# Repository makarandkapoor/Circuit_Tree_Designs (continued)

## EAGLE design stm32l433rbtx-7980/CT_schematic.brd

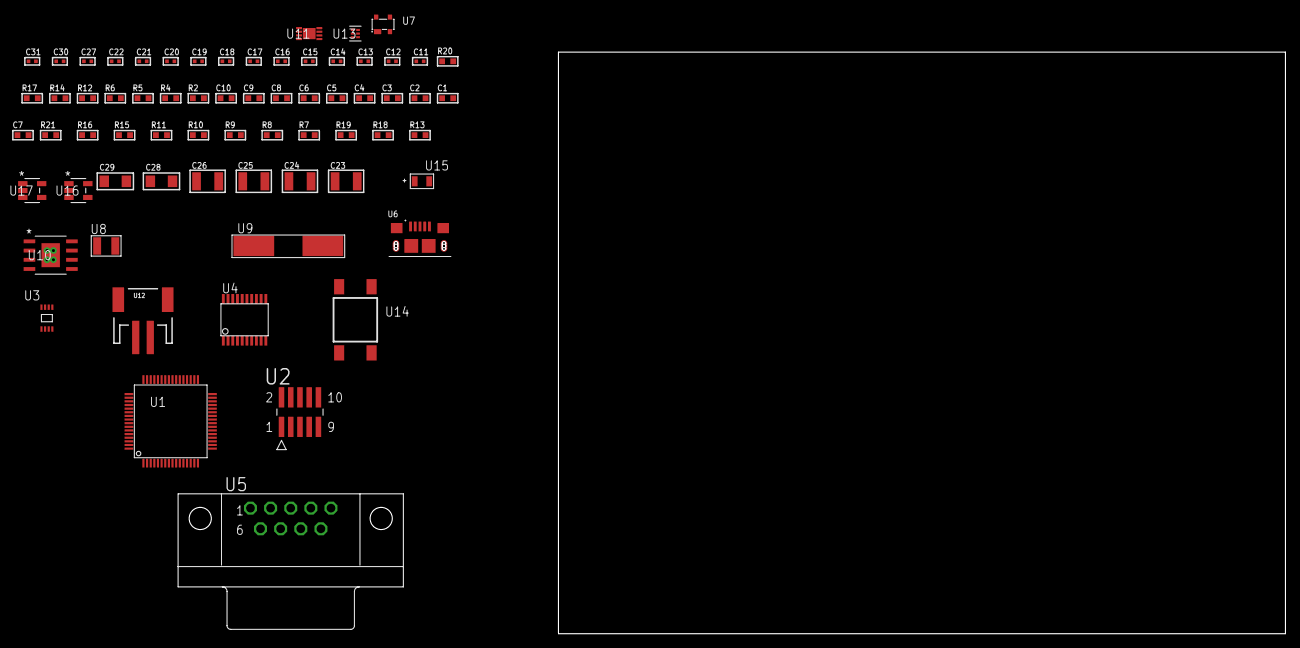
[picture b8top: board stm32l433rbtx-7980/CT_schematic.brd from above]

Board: 2 copper layers, 122.6 x 80.0 mm, 67 parts (0 on the bottom side), 42 nets, no tracks yet.

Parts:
C1, C9: 1e-06; C0603
C2, C3, C4, C5, C6, C10: 1e-07; C0603
C7: 4.7e-06; C0603
C8: 1e-08; C0603
C11, C12, C13, C14: 1e-11; C0402
C15, C17, C18, C19, C20, C21, C22, C27: 1e-07; C0402
C16, C30, C31: 1e-08; C0402
C23, C24, C25, C26: 1e-05; C1210
C28, C29: 1e-05; C1206
R2: 1000.0; R0603
R4: 4700.0; R0603
R5, R6, R14: 2200.0; R0603
R7, R8, R9, R10, R11, R15, R16, R21: 10000.0; R0603
R12: 5.0; R0603
R13: 4031.5447154472; R0603
R17: 9100.0; R0603
R18: 680000.0; R0603
R19: 120000.0; R0603
R20: 2000.0; R0603
U1: STM32L433RBT6; LQFP64
U2: FTSH-105-01-L-DV-K; SAMTEC_FTSH-105-01-L-DV-K
U3: 24AA16-I/MC; TDFN-8/6MM
U4: SP3203ECY-L/TR; TSSOP20-I
U5: 182-009-113R531; 182-009-MALE
U6: 10118193-0001LF; FCI_10118193-0001LF
U7: prtr5v0u2ax; SOT143B
U8: ABS07-32.768KHZ-7-T
U9: ABLS-25.000MHZ-B2F-T
U10: MIC5234YME; SOIC-8_EP
U11: MCP73831T-2ACI/MC; DFN8_2X3MC
U12: S2B-PH-SM4-TB(LF)(SN); JST-2-SMD
U13: TPS3895ADRYR; SON-6
U14: 4-1437565-2; SW_4-1437565-2
U15: Q65110A2395; LGM67K-G1J2-24-Z
U16, U17: nc7sz125m5x; NC7SZ125M5X

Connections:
CLK_CRYSTAL_U1_3: C11.1, U1.3, U8.1
CLK_CRYSTAL_U1_4: C12.1, U1.4, U8.2
CLK_CRYSTAL_U1_5: C13.1, U1.5, U9.1
CLK_CRYSTAL_U1_6: C14.1, U1.6, U9.2
GND: C1.2, C2.2, C3.2, C4.2, C5.2, C6.2, C7.2, C8.2, C9.2, C10.2, C11.2, C12.2, C13.2, C14.2, C15.2, C16.2, C17.2, C18.2, C21.2, C22.2, C23.2, C24.2, C25.2, C26.2, C27.2, C28.2, C29.2, C30.2, C31.2, R2.2, R7.2, R11.2, R12.2, R14.2, R17.2, R19.2, R20.2, U1.12, U1.18, U1.31, U1.47, U1.63, U2.3, U2.5, U3.4, U4.18, U5.5, U6.5, U6.6, U6.7, U6.8, U6.9, U7.1, U10.7, U10.EPAD, U11.6, U11.9, U12.2, U13.2, U15.C, U16.2, U16.3, U17.1, U17.3
INPUT_USBPOWER_5V: C28.1, R21.2, U6.1, U7.4, U11.1, U11.2
NET_U1_7: R4.1, U1.7, U17.4
NET_U1_42: R5.1, U1.42, U3.6
NET_U1_43: R6.1, U1.43, U3.5
NET_U1_60: R7.1, U1.60
NET_U1_62: U14.3, U14.4
NET_U2_9: R12.1, U2.9
NET_U4_1: C19.1, U4.1
NET_U4_2: C21.1, U4.2
NET_U4_3: C19.2, U4.3
NET_U4_4: C20.1, U4.4
NET_U4_5: C20.2, U4.5
NET_U4_6: C22.1, U4.6
NET_U5_2: U4.14, U5.2
NET_U5_3: U4.17, U5.3
NET_U5_7: U4.13, U5.7
NET_U5_8: U4.16, U5.8
NET_U10_4: R13.2, R14.1, U10.4
NET_U11_5: R21.1, U11.5
NET_U11_8: R20.1, U11.8
NET_U13_1: R16.1, R17.1, U13.1
NET_U13_3: R18.2, R19.1, U13.3
NET_U13_4: R15.1, U13.4, U16.4, U17.2
NET_U14_1: R2.1, U14.1, U14.2
PROC_LPUART1_CTS: U1.22, U4.8
PROC_LPUART1_RTS: U1.27, U4.10
PROC_LPUART1_RX: U1.8, U4.11
PROC_LPUART1_TX: U1.9, U4.7
PROC_SYS_JTCK_SWCLK: R11.1, U1.49, U2.4
PROC_SYS_JTDI: R9.1, U1.50, U2.8
PROC_SYS_JTDO_SWO: U1.55, U2.6
PROC_SYS_JTMS_SWDIO: R10.1, U1.46, U2.2
PROC_USB_DM: U1.44, U6.2, U7.3
PROC_USB_DP: U1.45, U6.3, U7.2
RST_OUT_U2_JTAG_RST_B: R8.1, U2.10, U16.1
VCC_S1_3V7: C23.1, C24.1, C29.1, U10.5, U10.8, U11.3, U11.4, U12.1
VCC_TIER1_3V3: C1.1, C2.1, C3.1, C4.1, C5.1, C6.1, C7.1, C8.1, C9.1, C10.1, C15.1, C16.1, C17.1, C18.1, C25.1, C26.1, C27.1, C30.1, C31.1, R4.2, R5.2, R6.2, R8.2, R9.2, R10.2, R13.1, R15.2, R16.2, R18.1, U1.1, U1.13, U1.19, U1.32, U1.48, U1.64, U2.1, U3.7, U3.8, U4.12, U4.19, U10.1, U13.6, U16.5, U17.5
